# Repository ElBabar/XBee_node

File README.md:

# XBee_node
Node for CANbus and XBee commuincation

This node is a rackable board for a robot taking part in the Coupe de France de Robotique.

It allows the system to communicate using both CANbus and XBee, using a homemade adapter (see XBeeSX868_adapter).

You might need to use my library:
add https://github.com/ElBabar/Libabar.git
to your KiCad paths.

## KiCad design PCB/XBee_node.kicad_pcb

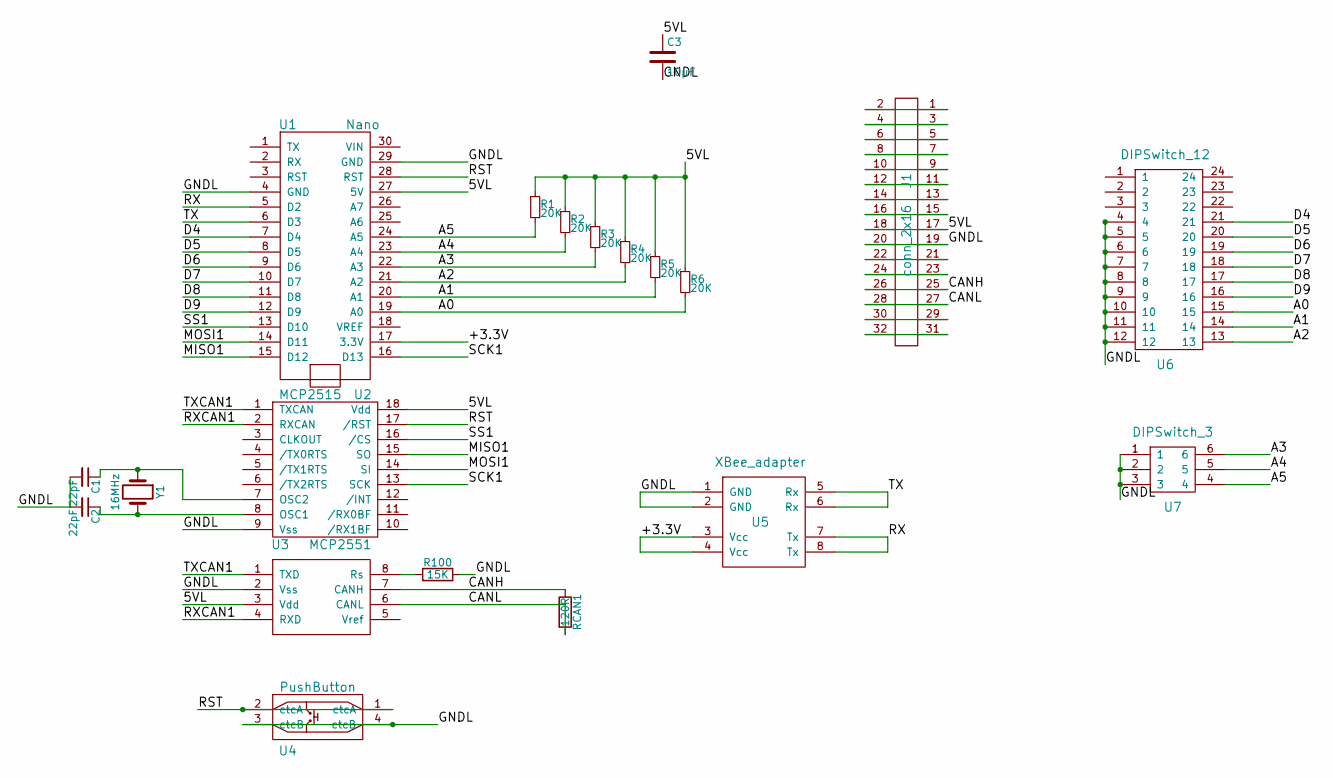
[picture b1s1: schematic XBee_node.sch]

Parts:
C1, C2: 22pF; C_0805_HandSoldering
C3: 10µF; CP_Radial_D6.3mm_P2.50mm
J1: conn_2x16
R1, R2, R3, R4, R5, R6: 20K; R_0805_HandSoldering
R100: 15K; R_Axial_DIN0207_L6.3mm_D2.5mm_P10.16mm_Horizontal
RCAN1: 120R; R_Axial_DIN0207_L6.3mm_D2.5mm_P10.16mm_Horizontal
U1: Nano
U2: MCP2515; DIP-18_W7.62mm
U3: MCP2551; DIP-8_W7.62mm
U4: PushButton
U5: XBee_adapter
U6: DIPSwitch_12
U7: DIPSwitch_3
Y1: 16MHz; Resonator-2pin_w10.0mm_h5.0mm

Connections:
/5VL: C3.1, J1.17, J1.18, R1.1, R2.1, R3.1, R4.1, R5.1, R6.1, U1.27 (5V), U2.18 (Vdd), U3.3 (Vdd)
/+3.3V: U1.17 (3.3V), U5.3 (Vcc), U5.4 (Vcc)
/A0: R6.2, U1.19 (A0), U6.15
/A1: R5.2, U1.20 (A1), U6.14
/A2: R4.2, U1.21 (A2), U6.13
/A3: R3.2, U1.22 (A3), U7.6
/A4: R2.2, U1.23 (A4), U7.5
/A5: R1.2, U1.24 (A5), U7.4
/CANH: J1.25, J1.26, RCAN1.1, U3.7 (CANH)
/CANL: J1.27, J1.28, RCAN1.2, U3.6 (CANL)
/D4: U1.7 (D4), U6.21
/D5: U1.8 (D5), U6.20
/D6: U1.9 (D6), U6.19
/D7: U1.10 (D7), U6.18
/D8: U1.11 (D8), U6.17
/D9: U1.12 (D9), U6.16
/GNDL: C1.2, C2.2, C3.2, J1.19, J1.20, R100.2, U1.4 (GND), U1.29 (GND), U2.9 (Vss), U3.2 (Vss), U4.3 (ctcB), U4.4 (ctcB), U5.1 (GND), U5.2 (GND), U6.4, U6.5, U6.6, U6.7, U6.8, U6.9, U6.10, U6.11, U6.12, U7.1, U7.2, U7.3
/MISO1: U1.15 (D12), U2.15 (SO)
/MOSI1: U1.14 (D11), U2.14 (SI)
/RST: U1.28 (RST), U2.17 (/RST), U4.1 (ctcA), U4.2 (ctcA)
/RX: U1.5 (D2), U5.7 (Tx), U5.8 (Tx)
/RXCAN1: U2.2 (RXCAN), U3.4 (RXD)
/SCK1: U1.16 (D13), U2.13 (SCK)
/SS1: U1.13 (D10), U2.16 (/CS)
/TX: U1.6 (D3), U5.5 (Rx), U5.6 (Rx)
/TXCAN1: U2.1 (TXCAN), U3.1 (TXD)
unnamed: C1.1, U2.7 (OSC2), Y1.1
unnamed: C2.1, U2.8 (OSC1), Y1.2
unnamed: J1.1, J1.2
unnamed: J1.3, J1.4
unnamed: J1.5, J1.6
unnamed: J1.7, J1.8
unnamed: J1.9, J1.10
unnamed: J1.11, J1.12
unnamed: J1.13, J1.14
unnamed: J1.15, J1.16
unnamed: J1.21, J1.22
unnamed: J1.23, J1.24
unnamed: J1.29, J1.30
unnamed: J1.31, J1.32
unnamed: R100.1, U3.8 (Rs)

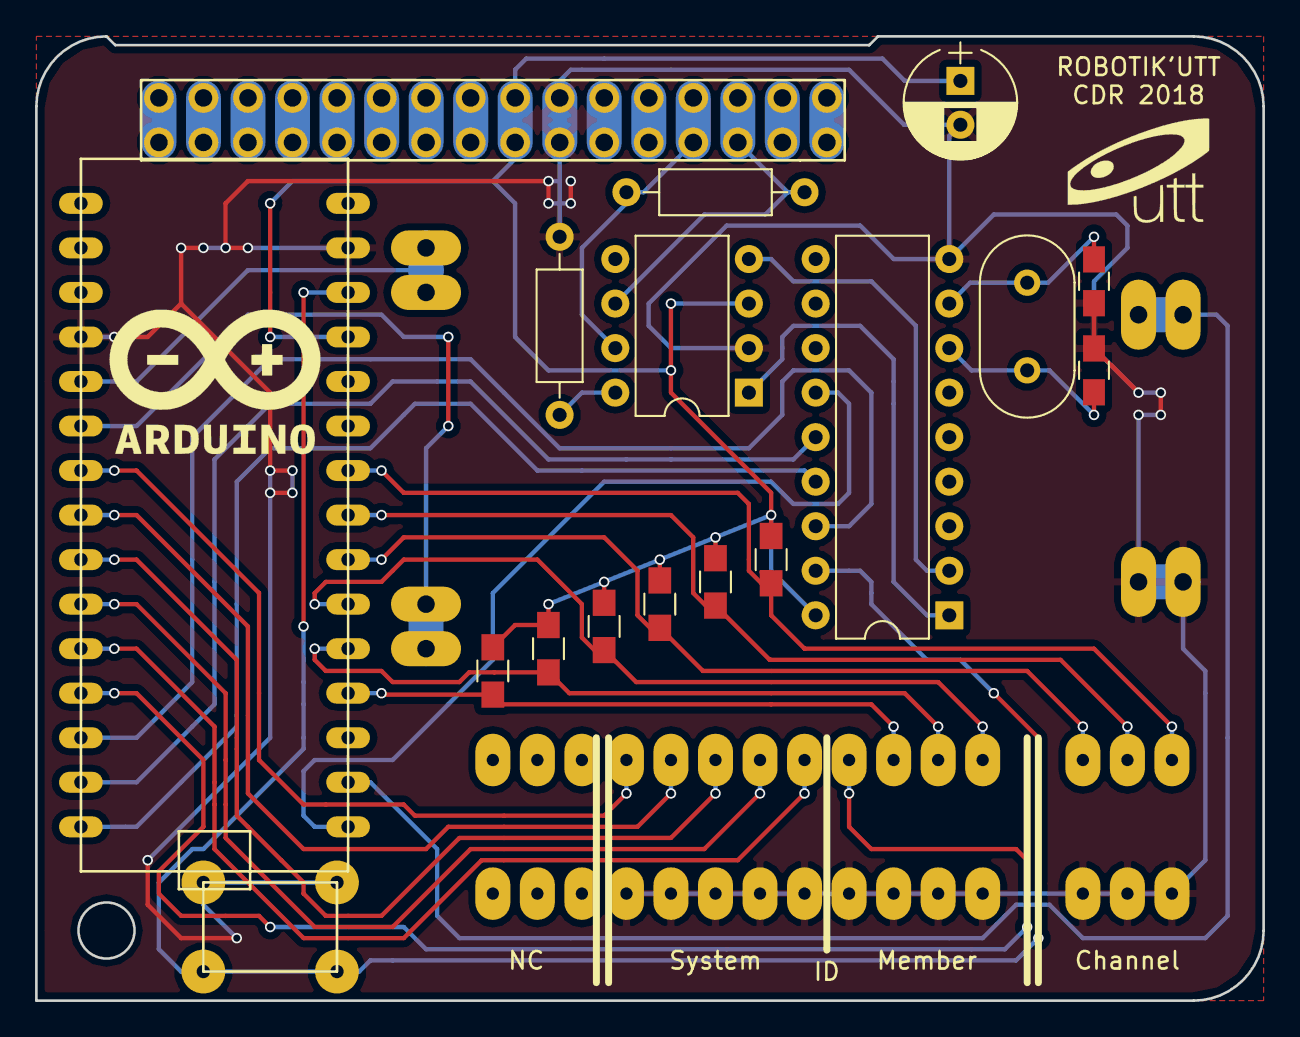
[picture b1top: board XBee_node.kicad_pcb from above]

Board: 2 copper layers, 70.0 x 55.0 mm, 20 parts (0 on the bottom side), 41 nets.

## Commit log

2017-12-08 Changed tree
2017-12-08 Moved Readme
2018-01-28 reduced ID to implement SoftwareSerial
